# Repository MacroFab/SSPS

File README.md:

***
###SSPS
***
**MacroFab, INC. Super Simple Power Supply**

This repository contains the information and files needed to build the Super Simple Power Supply or SSPS. 

More information can be found on the [MacroFab, INC. blog](https://macrofab.com/blog/tag/ssps/). 

***
**License Information**

This project is under the [Creative Commons Attribution-ShareAlike 4.0 International License](LICENSE.md). These files are provided with no warranty and should be used at your own risk. 

***

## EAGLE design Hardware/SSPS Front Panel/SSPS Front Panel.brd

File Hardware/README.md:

***
###Hardware
***
**Hardware for the Super Simple Power Supply**

This repository contains the information and files needed to build the Super Simple Power Supply or SSPS. 

More information can be found on the [MacroFab, INC. blog](https://macrofab.com/blog/tag/ssps/). Specifications can be found [here](https://macrofab.com/blog/super-simple-power-supply-ssps-design-part-1/).

***
**License Information**

This project is under the [Creative Commons Attribution-ShareAlike 4.0 International License](LICENSE.md). These files are provided with no warranty and should be used at your own risk. 

***
**Directory listing of the repository**

| Directory | Description |
|---|---|
| Datasheets |  Datasheets that are a pain to get a hold of. |
| Enclosure | Enclosure Drawings and Mockups. | 
| OPA541 Breakout | Test board for the OPA541 Opamp. |
| SSPS Front Panel | Front Panel for the SSPS. Digital Controls. |
| SSPS Front Panel Test | Test board for the SSPS digital side. |
| SSPS Analog board | Analog output board |
| SSPS Regulated Power Supply Simulation | Multisim Simulation of the SSPS Analog side. |

***
**Credits**

Designed by:   
Parker Dillmann 
Stephen "Hackerman" Kraig 

Software by:   
Parker Dillmann  
Stephen "Hackerman" Kraig 

***

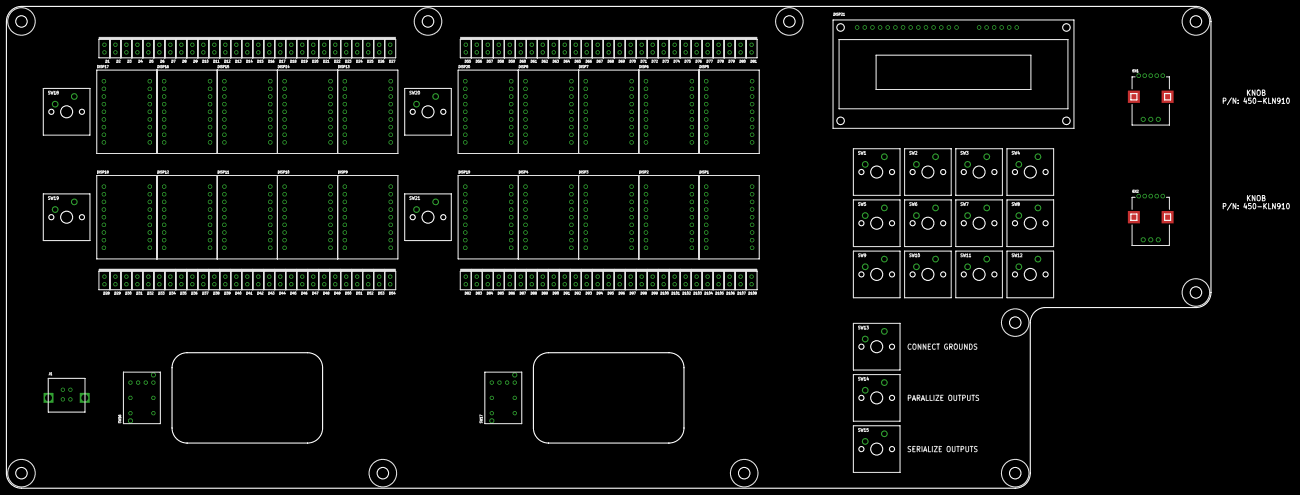
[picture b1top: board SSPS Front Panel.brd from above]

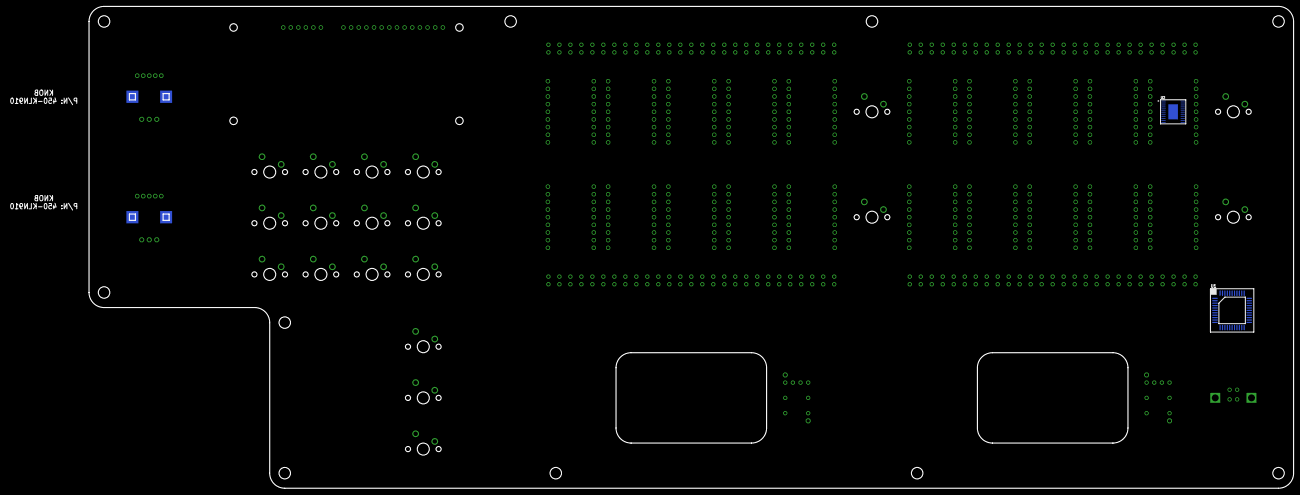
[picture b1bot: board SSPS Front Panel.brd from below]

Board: 2 copper layers, 400.0 x 160.0 mm, 165 parts (2 on the bottom side), 3 nets, no tracks yet.

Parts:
D1, D2, D3, D4, D5, D6, D7, D8, D9, D10, D11, D12, D13, D14, D15, D16, D17, D18, D19, D20, D21, D22, D23, D24, D25, D26, D27, D28, D29, D30, D31, D32, D33, D34, D35, D36, D37, D38, D39, D40, D41, D42, D43, D44, D45, D46, D47, D48, D49, D50, D51, D52, D53, D54, D55, D56, D57, D58, D59, D60, D61, D62, D63, D64, D65, D66, D67, D68, D69, D70, D71, D72, D73, D74, D75, D76, D77, D78, D79, D80, D81, D82, D83, D84, D85, D86, D87, D88, D89, D90, D91, D92, D93, D94, D95, D96, D97, D98, D99, D100, D101, D102, D103, D104, D105, D106, D107, D108: WP1043
DISP1, DISP2, DISP3, DISP4, DISP5, DISP6, DISP7, DISP8, DISP9, DISP10, DISP11, DISP12, DISP13, DISP14, DISP15, DISP16, DISP17, DISP18, DISP19, DISP20: PSA08-11GWA; PSA08-11SRWA
DISP21: CU16025-UWJ6; CU16025-UW6J
EN1, EN2: PEL12T-4226F-S1024; PEL12T
H1, H2, H3, H4, H5, H6, H7, H8, H9, H10: MOUNT_HOLE_150MIL
J1: 61400413321
SW1, SW2, SW3, SW4, SW5, SW6, SW7, SW8, SW9, SW10, SW11, SW12, SW13, SW14, SW15, SW18, SW19, SW20, SW21: MX1A
SW16, SW17: 5501
U1: P8X32A-Q44; LQFP44
U2: STP16CP05XTTR; STP16CP05XTTR_TTSOP-24

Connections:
SLD: J1.S1, J1.S2
VDD: U1.8, U1.18, U1.30, U1.40
VSS: U1.5, U1.17, U1.27, U1.39

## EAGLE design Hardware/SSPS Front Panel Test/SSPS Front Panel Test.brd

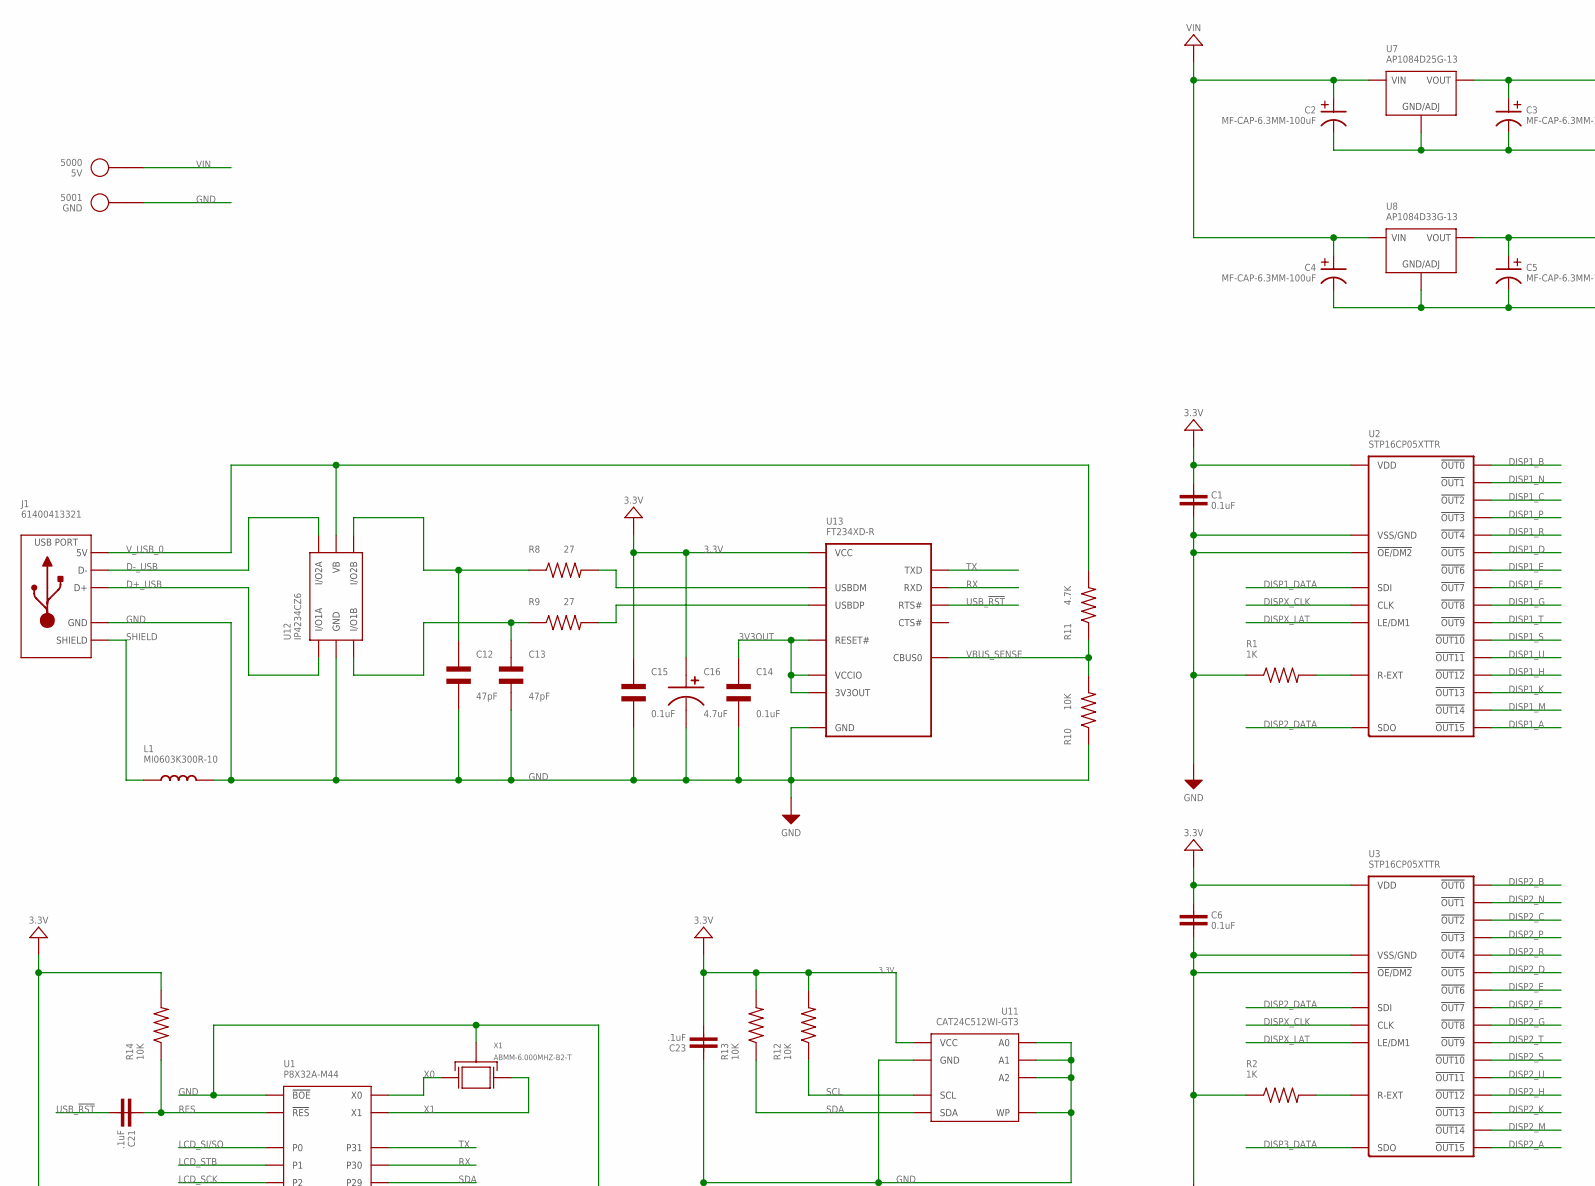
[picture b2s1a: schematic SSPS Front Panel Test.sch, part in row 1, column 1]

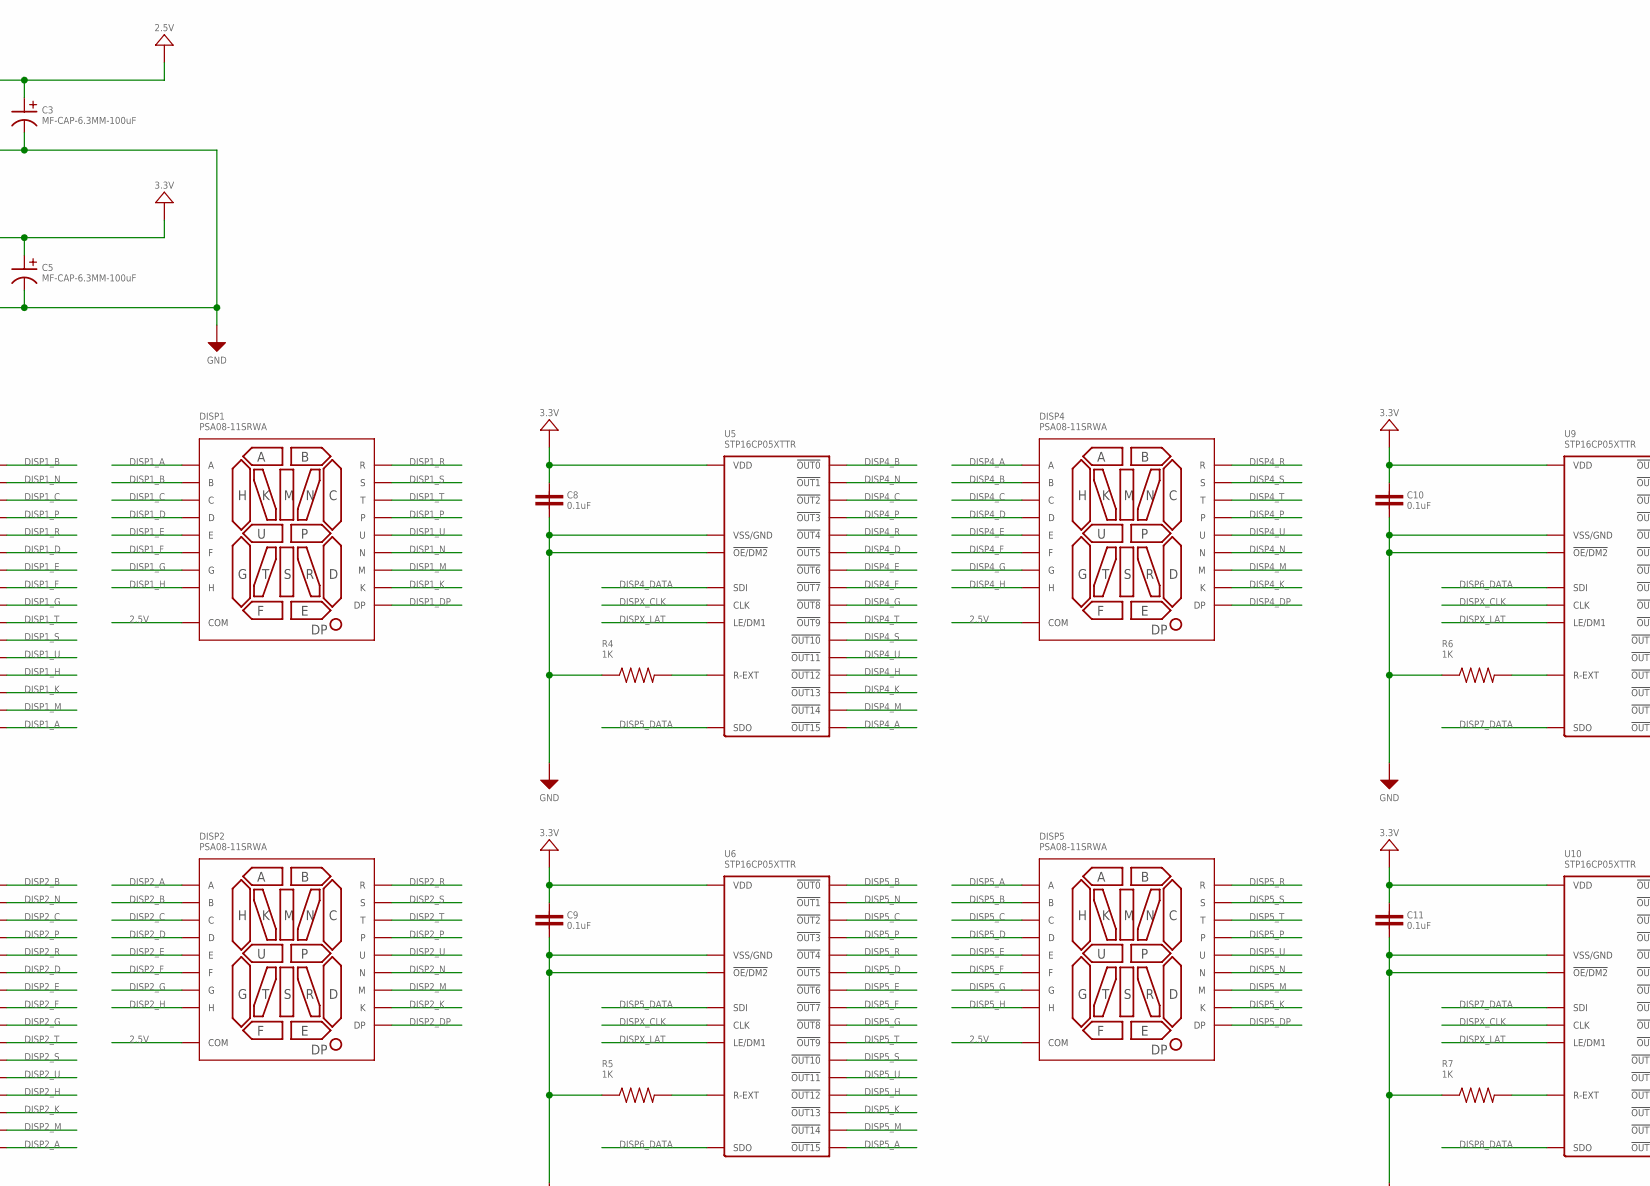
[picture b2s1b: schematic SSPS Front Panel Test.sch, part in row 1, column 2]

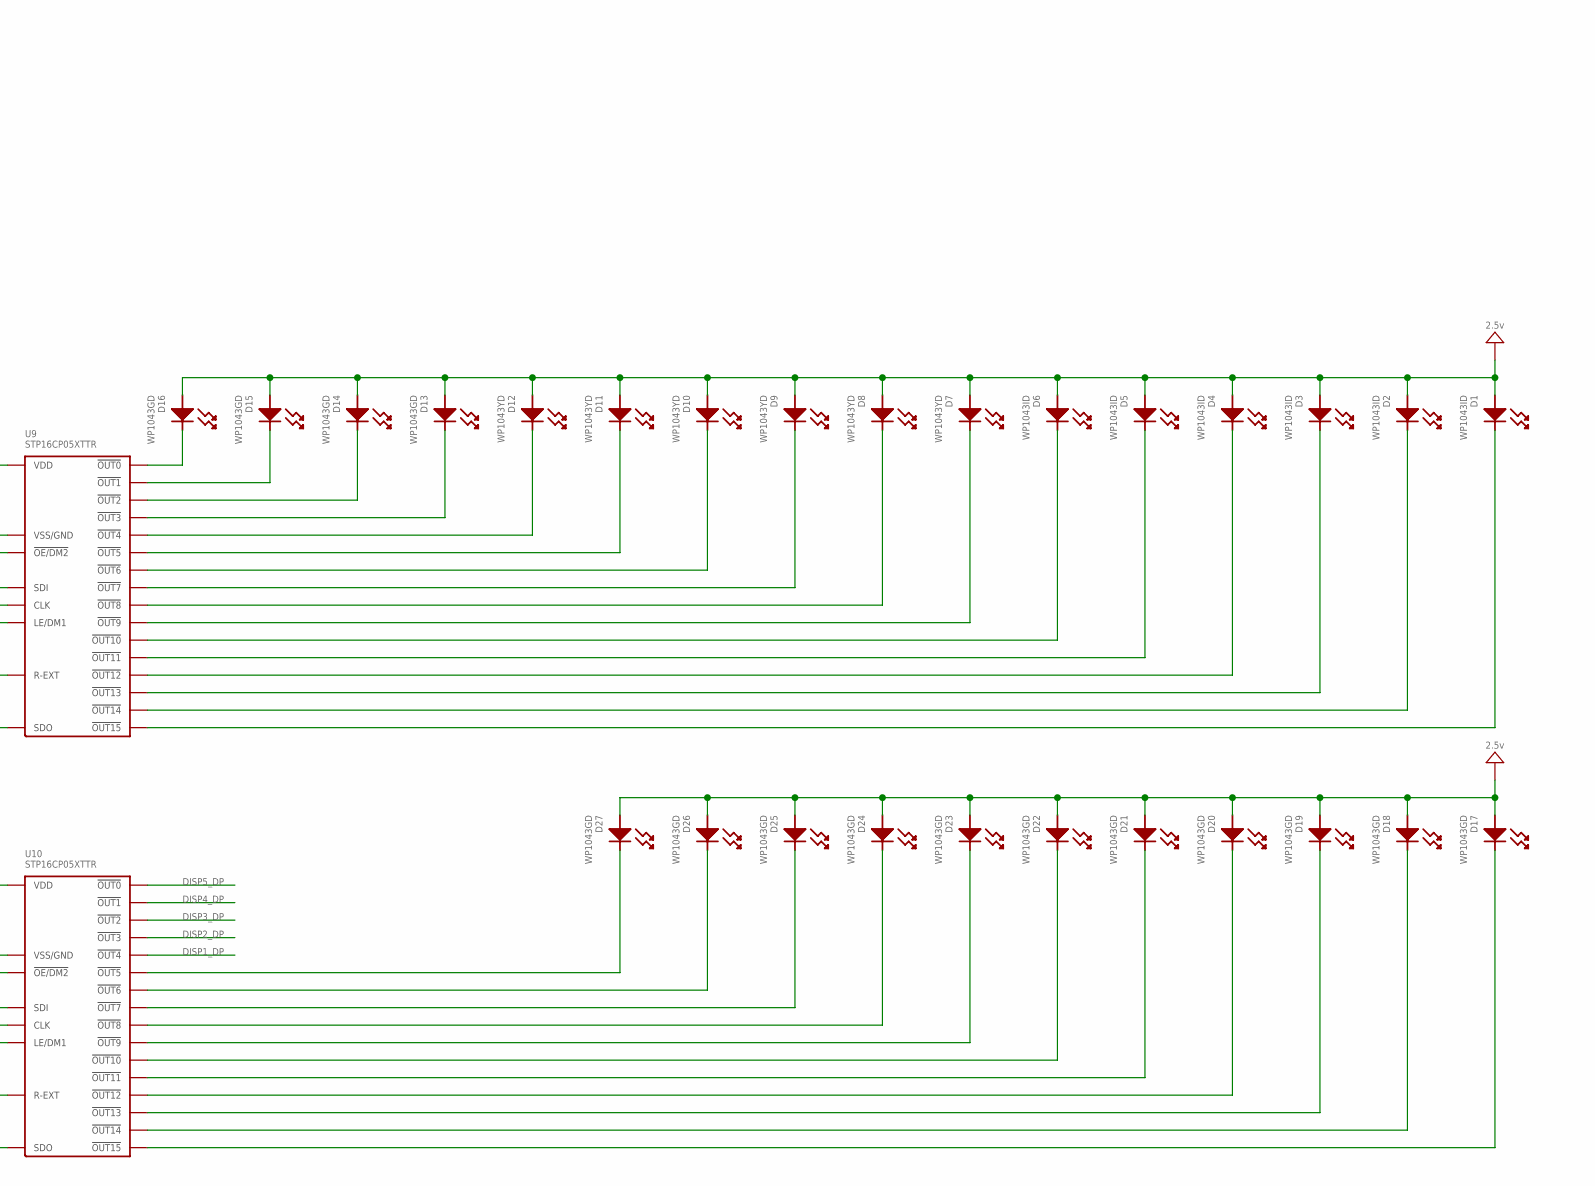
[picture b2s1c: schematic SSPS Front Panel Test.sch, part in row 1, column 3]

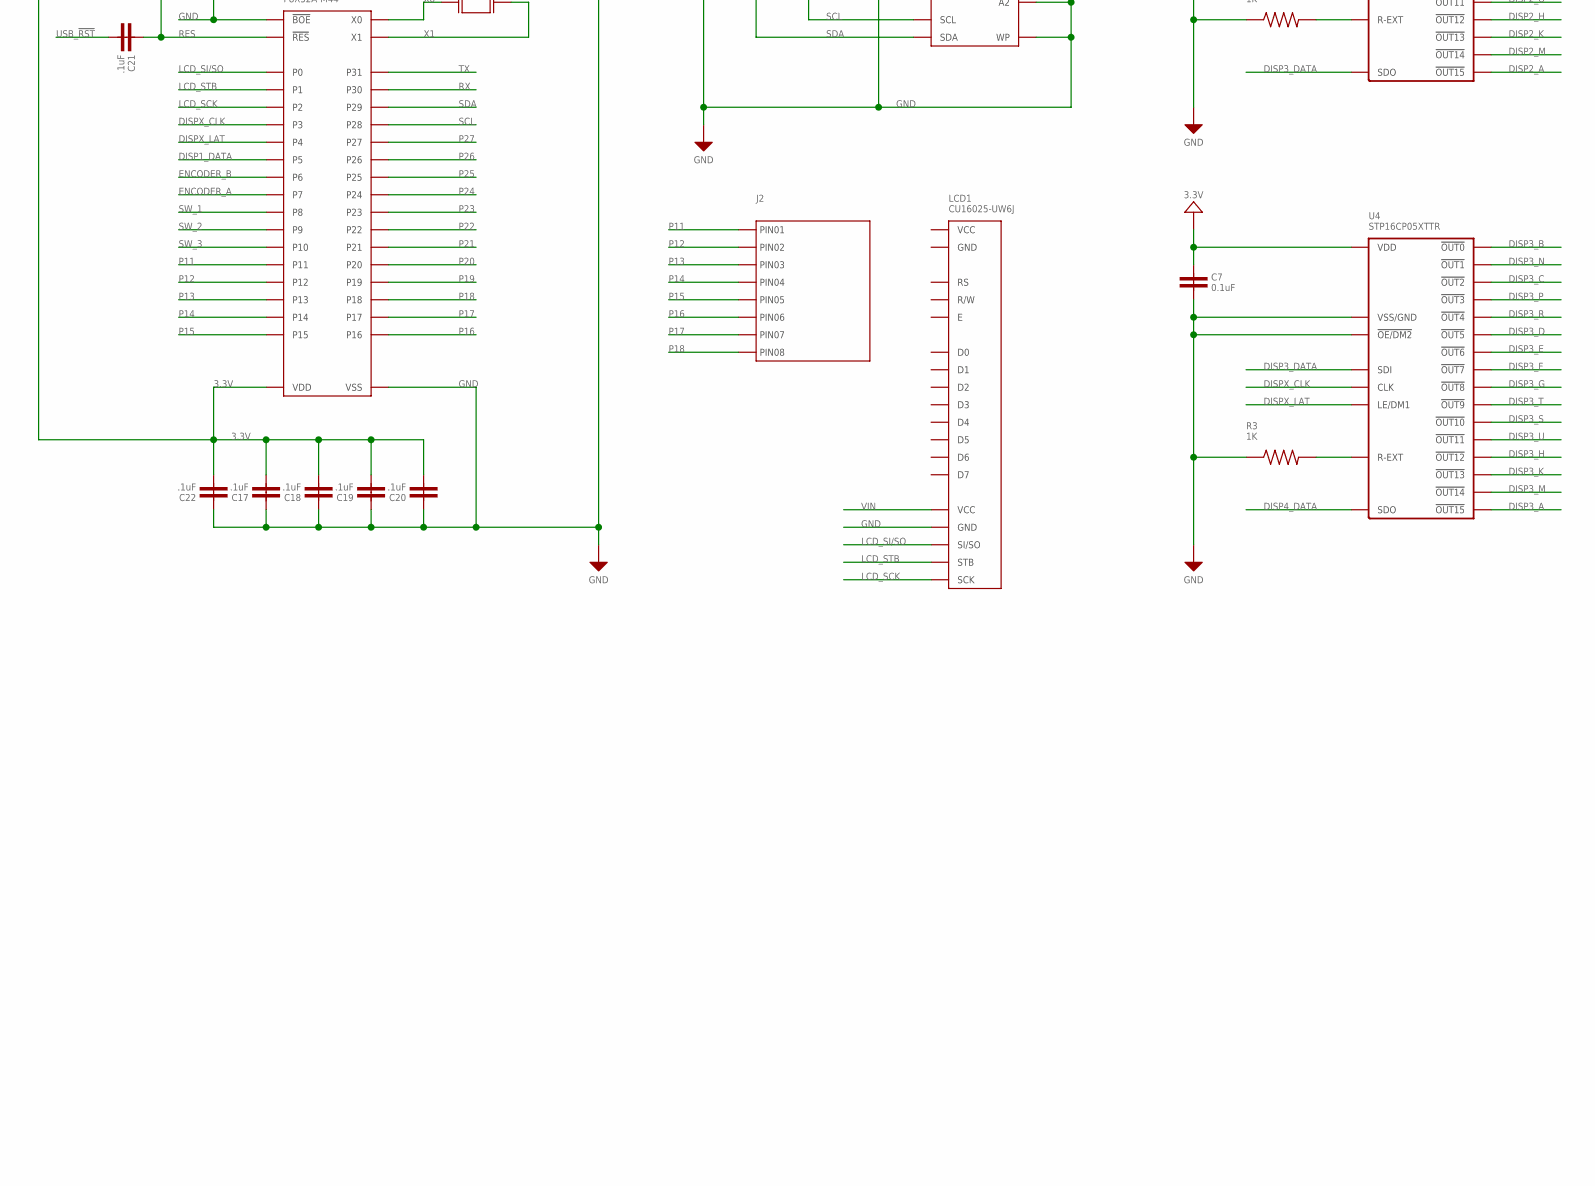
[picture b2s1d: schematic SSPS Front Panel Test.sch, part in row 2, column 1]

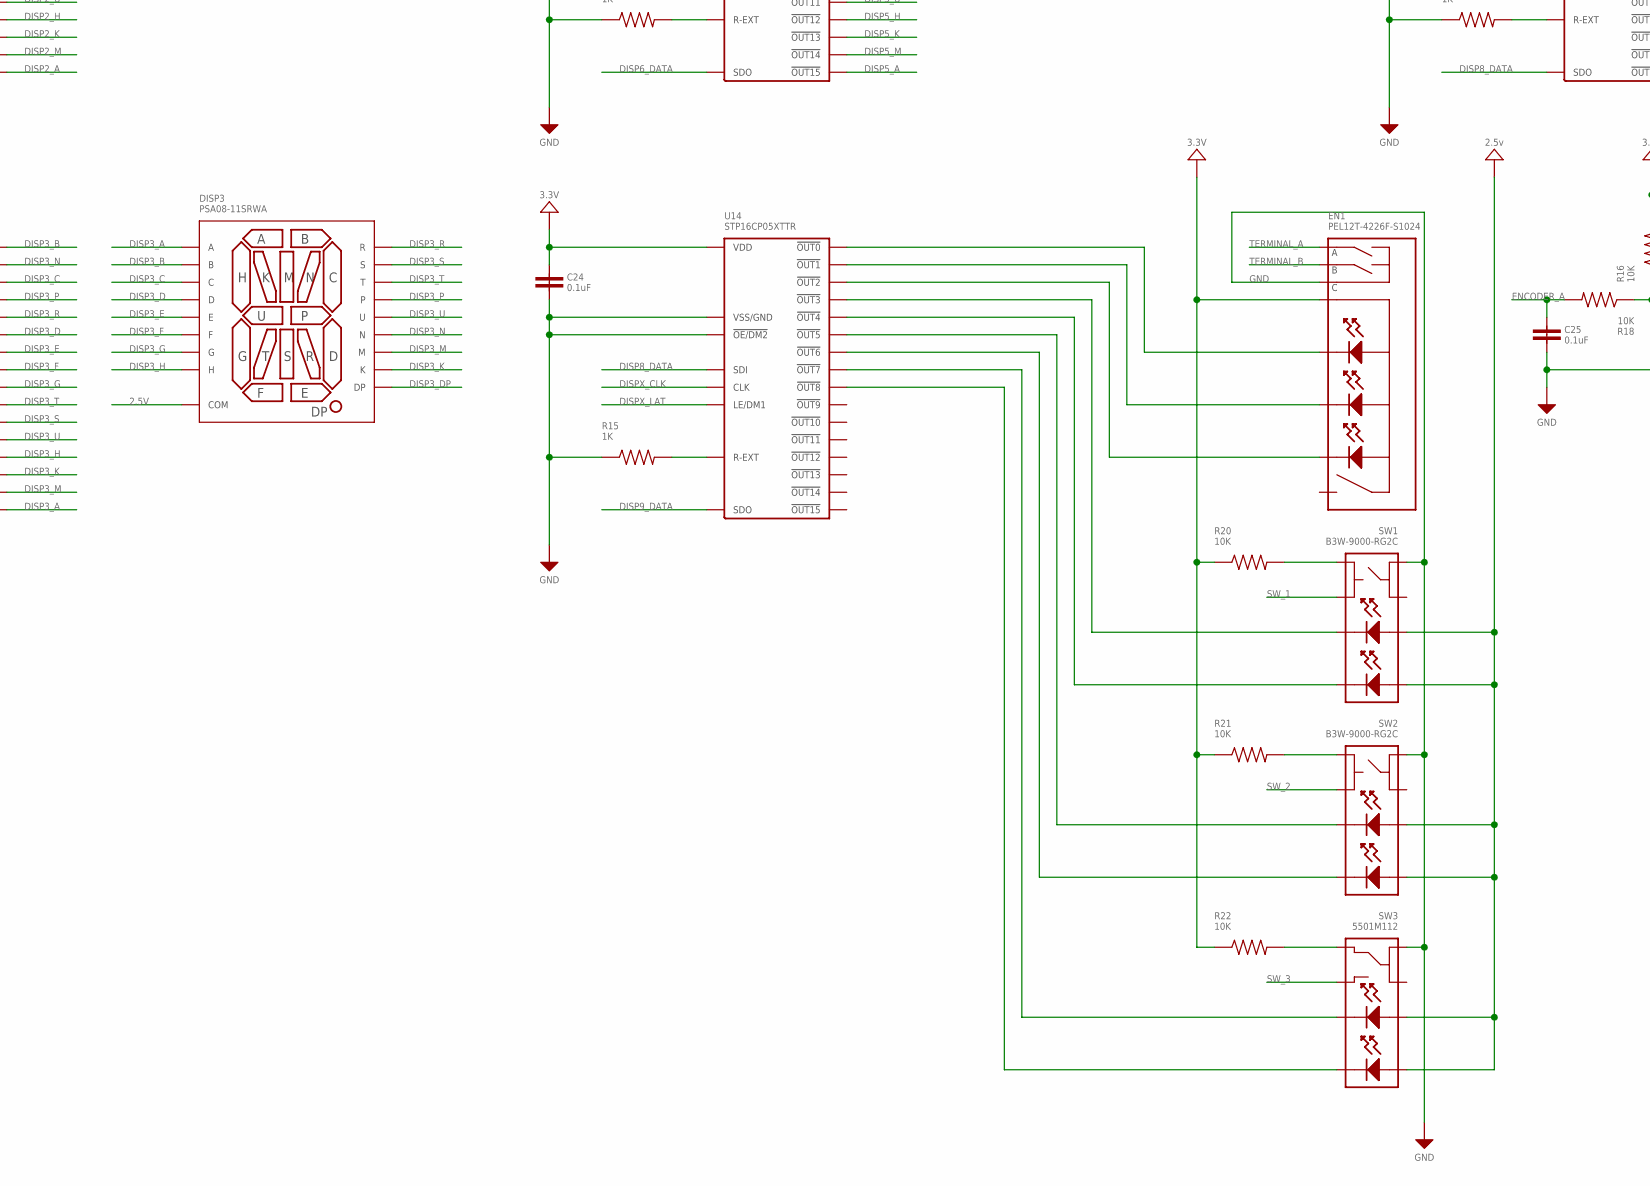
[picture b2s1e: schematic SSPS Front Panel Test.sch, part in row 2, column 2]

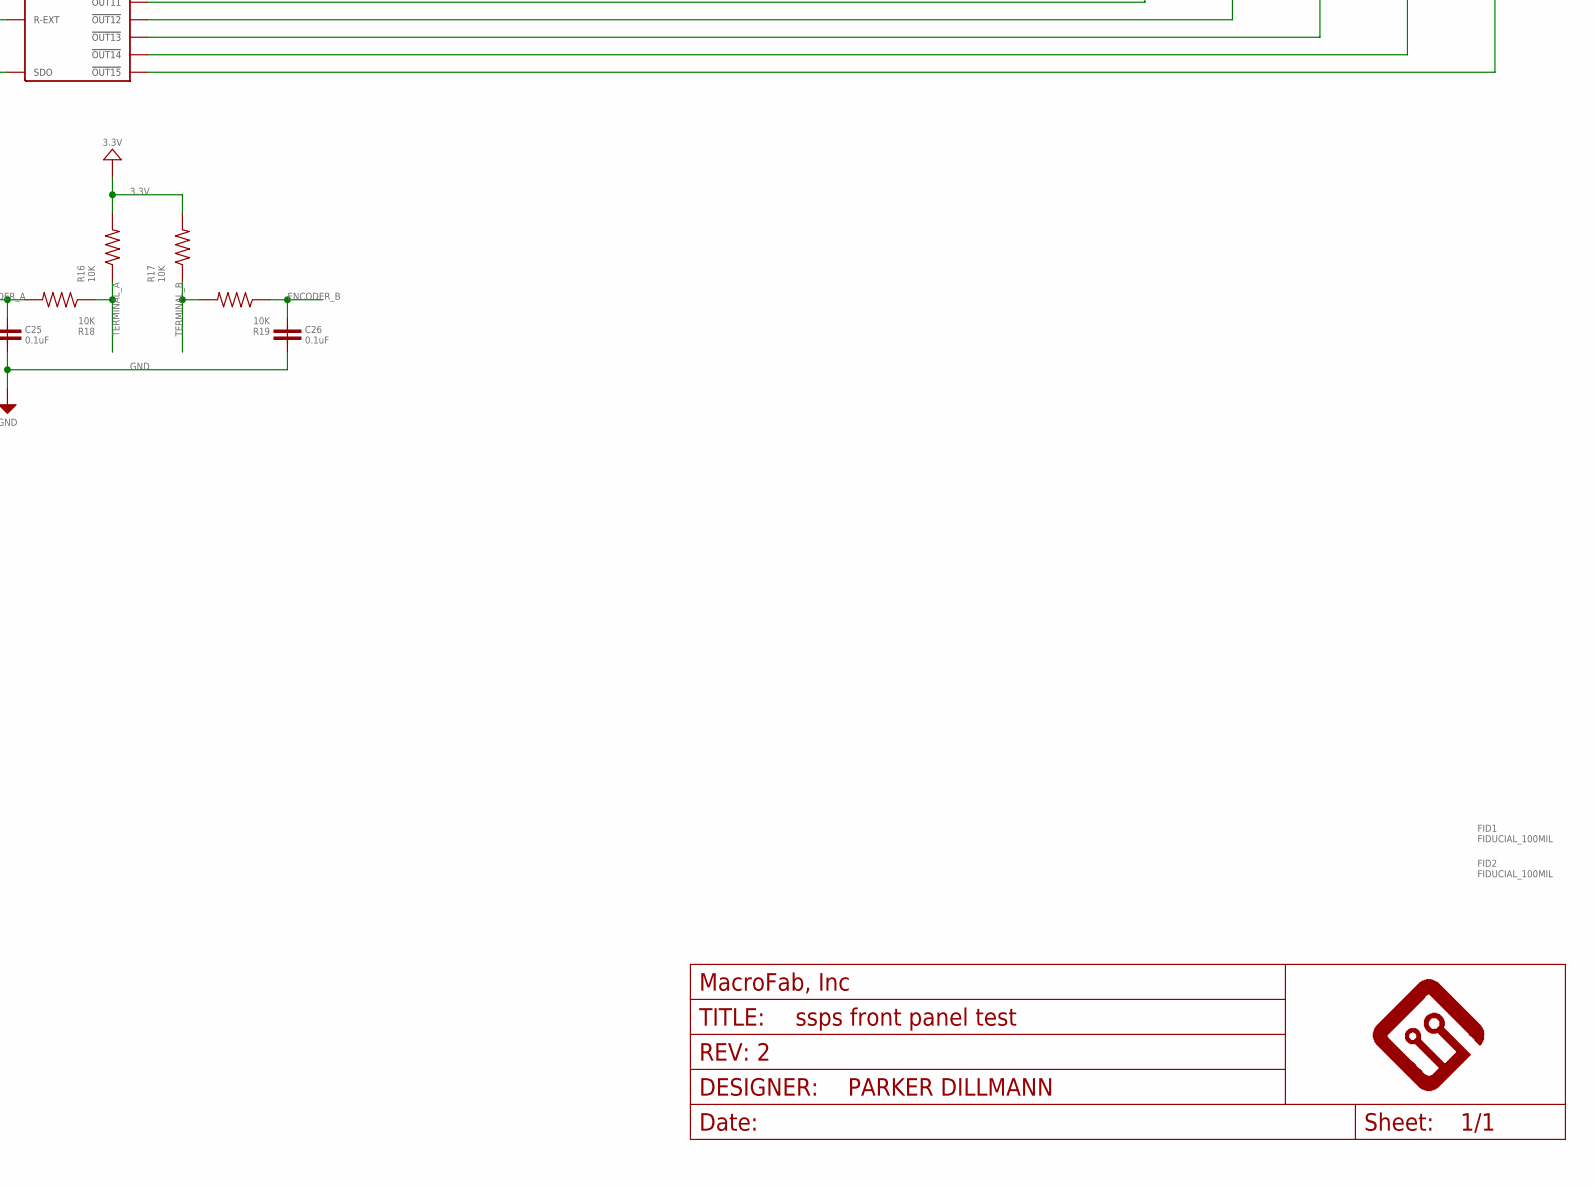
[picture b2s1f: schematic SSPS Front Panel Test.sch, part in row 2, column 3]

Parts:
5V: 5000; KEYSTONE_5115-5119
C1, C6, C7, C8, C9, C10, C11, C24, C25, C26: 0.1uF; 0603
C2, C3, C4, C5: MF-CAP-6.3MM-100uF; 6.3MM_CAP_SMD
C12, C13: 47pF; C0603
C14, C15: 0.1uF; C0603
C16: 4.7uF; CP4MM
C17, C18, C19, C20, C21, C22, C23: .1uF; 0603
D1, D2, D3, D4, D5, D6: WP1043ID; WP1043
D7, D8, D9, D10, D11, D12: WP1043YD; WP1043
D13, D14, D15, D16, D17, D18, D19, D20, D21, D22, D23, D24, D25, D26, D27: WP1043GD; WP1043
DISP1, DISP2, DISP3, DISP4, DISP5: PSA08-11SRWA
EN1: PEL12T-4226F-S1024; PEL12T
FID1, FID2: FIDUCIAL_100MIL
FRAME1: MF_FRAMEDEFAULT; MF_FRAME_DEFAULT
GND: 5001; KEYSTONE_5115-5119
J1: 61400413321
J2: CON_01X08_2.54MM_PIN_HEADER; 2.54MM_01X08_PIN_HEADER
L1: MI0603K300R-10; L0603
LCD1: CU16025-UW6J
R1, R2, R3, R4, R5, R6, R7, R15: 1K; 0603
R8, R9: 27; R0603
R10: 10K; R0603
R11: 4.7K; R0603
R12, R13, R14, R16, R17, R18, R19, R20, R21, R22: 10K; 0603
SW1, SW2: B3W-9000-RG2C; B3W-9000
SW3: 5501M112; 5501
U1: P8X32A-M44; P8X32A_QFN-44
U2, U3, U4, U5, U6, U9, U10, U14: STP16CP05XTTR; STP16CP05XTTR_TTSOP-24
U7: AP1084D25G-13; AP1084_TO-252-3L
U8: AP1084D33G-13; AP1084_TO-252-3L
U11: CAT24C512WI-GT3; SOIC-8_W
U12: IP4234CZ6; IP4234CZ6_SOT-457-6
U13: FT234XD-R; FT234X_DFN-12
X1: ABMM-6.000MHZ-B2-T; 7MMX5MM

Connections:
2.5V: C3.POS, D1.A (ANODE), D2.A (ANODE), D3.A (ANODE), D4.A (ANODE), D5.A (ANODE), D6.A (ANODE), D7.A (ANODE), D8.A (ANODE), D9.A (ANODE), D10.A (ANODE), D11.A (ANODE), D12.A (ANODE), D13.A (ANODE), D14.A (ANODE), D15.A (ANODE), D16.A (ANODE), D17.A (ANODE), D18.A (ANODE), D19.A (ANODE), D20.A (ANODE), D21.A (ANODE), D22.A (ANODE), D23.A (ANODE), D24.A (ANODE), D25.A (ANODE), D26.A (ANODE), D27.A (ANODE), DISP1.P$11 (COM), DISP2.P$11 (COM), DISP3.P$11 (COM), DISP4.P$11 (COM), DISP5.P$11 (COM), SW1.ANODE_1, SW1.ANODE_2, SW2.ANODE_1, SW2.ANODE_2, SW3.ANODE_1, SW3.ANODE_2, U7.3 (OUT)
3.3V: C1.1, C5.POS, C6.1, C7.1, C8.1, C9.1, C10.1, C11.1, C15.P$1, C16.P$1, C17.2, C18.2, C19.2, C20.2, C22.2, C23.2, C24.1, EN1.5, R12.2, R13.2, R14.2, R16.2, R17.2, R20.1, R21.1, R22.1, U1.8 (VDD), U1.18 (VDD), U1.30 (VDD), U1.40 (VDD), U2.P$24 (VDD), U3.P$24 (VDD), U4.P$24 (VDD), U5.P$24 (VDD), U6.P$24 (VDD), U8.3 (OUT), U9.P$24 (VDD), U10.P$24 (VDD), U11.8 (VCC), U13.4 (VCC), U14.P$24 (VDD)
3V3OUT: C14.P$1, U13.2 (RESET#), U13.3 (3V3OUT), U13.9 (VCCIO)
D+_USB: J1.3 (D+), U12.1 (I/O1A)
D-_USB: J1.2 (D-), U12.6 (I/O2A)
DISP1_A: DISP1.P$1 (A), U2.P$20 (!OUT15)
DISP1_B: DISP1.P$18 (B), U2.P$5 (!OUT0)
DISP1_C: DISP1.P$16 (C), U2.P$7 (!OUT2)
DISP1_D: DISP1.P$13 (D), U2.P$10 (!OUT5)
DISP1_DATA: U1.2 (P5), U2.P$2 (SDI)
DISP1_DP: DISP1.P$12 (DP), U10.P$9 (!OUT4)
DISP1_E: DISP1.P$10 (E), U2.P$11 (!OUT6)
DISP1_F: DISP1.P$9 (F), U2.P$12 (!OUT7)
DISP1_G: DISP1.P$8 (G), U2.P$13 (!OUT8)
DISP1_H: DISP1.P$4 (H), U2.P$17 (!OUT12)
DISP1_K: DISP1.P$3 (K), U2.P$18 (!OUT13)
DISP1_M: DISP1.P$2 (M), U2.P$19 (!OUT14)
DISP1_N: DISP1.P$17 (N), U2.P$6 (!OUT1)
DISP1_P: DISP1.P$15, U2.P$8 (!OUT3)
DISP1_R: DISP1.P$14 (R), U2.P$9 (!OUT4)
DISP1_S: DISP1.P$6 (S), U2.P$15 (!OUT10)
DISP1_T: DISP1.P$7 (T), U2.P$14 (!OUT9)
DISP1_U: DISP1.P$5 (U), U2.P$16 (!OUT11)
DISP2_A: DISP2.P$1 (A), U3.P$20 (!OUT15)
DISP2_B: DISP2.P$18 (B), U3.P$5 (!OUT0)
DISP2_C: DISP2.P$16 (C), U3.P$7 (!OUT2)
DISP2_D: DISP2.P$13 (D), U3.P$10 (!OUT5)
DISP2_DATA: U2.P$22 (SDO), U3.P$2 (SDI)
DISP2_DP: DISP2.P$12 (DP), U10.P$8 (!OUT3)
DISP2_E: DISP2.P$10 (E), U3.P$11 (!OUT6)
DISP2_F: DISP2.P$9 (F), U3.P$12 (!OUT7)
DISP2_G: DISP2.P$8 (G), U3.P$13 (!OUT8)
DISP2_H: DISP2.P$4 (H), U3.P$17 (!OUT12)
DISP2_K: DISP2.P$3 (K), U3.P$18 (!OUT13)
DISP2_M: DISP2.P$2 (M), U3.P$19 (!OUT14)
DISP2_N: DISP2.P$17 (N), U3.P$6 (!OUT1)
DISP2_P: DISP2.P$15, U3.P$8 (!OUT3)
DISP2_R: DISP2.P$14 (R), U3.P$9 (!OUT4)
DISP2_S: DISP2.P$6 (S), U3.P$15 (!OUT10)
DISP2_T: DISP2.P$7 (T), U3.P$14 (!OUT9)
DISP2_U: DISP2.P$5 (U), U3.P$16 (!OUT11)
DISP3_A: DISP3.P$1 (A), U4.P$20 (!OUT15)
DISP3_B: DISP3.P$18 (B), U4.P$5 (!OUT0)
DISP3_C: DISP3.P$16 (C), U4.P$7 (!OUT2)
DISP3_D: DISP3.P$13 (D), U4.P$10 (!OUT5)
DISP3_DATA: U3.P$22 (SDO), U4.P$2 (SDI)
DISP3_DP: DISP3.P$12 (DP), U10.P$7 (!OUT2)
DISP3_E: DISP3.P$10 (E), U4.P$11 (!OUT6)
DISP3_F: DISP3.P$9 (F), U4.P$12 (!OUT7)
DISP3_G: DISP3.P$8 (G), U4.P$13 (!OUT8)
DISP3_H: DISP3.P$4 (H), U4.P$17 (!OUT12)
DISP3_K: DISP3.P$3 (K), U4.P$18 (!OUT13)
DISP3_M: DISP3.P$2 (M), U4.P$19 (!OUT14)
DISP3_N: DISP3.P$17 (N), U4.P$6 (!OUT1)
DISP3_P: DISP3.P$15, U4.P$8 (!OUT3)
DISP3_R: DISP3.P$14 (R), U4.P$9 (!OUT4)
DISP3_S: DISP3.P$6 (S), U4.P$15 (!OUT10)
DISP3_T: DISP3.P$7 (T), U4.P$14 (!OUT9)
DISP3_U: DISP3.P$5 (U), U4.P$16 (!OUT11)
DISP4_A: DISP4.P$1 (A), U5.P$20 (!OUT15)
DISP4_B: DISP4.P$18 (B), U5.P$5 (!OUT0)
DISP4_C: DISP4.P$16 (C), U5.P$7 (!OUT2)
DISP4_D: DISP4.P$13 (D), U5.P$10 (!OUT5)
DISP4_DATA: U4.P$22 (SDO), U5.P$2 (SDI)
DISP4_DP: DISP4.P$12 (DP), U10.P$6 (!OUT1)
DISP4_E: DISP4.P$10 (E), U5.P$11 (!OUT6)
DISP4_F: DISP4.P$9 (F), U5.P$12 (!OUT7)
DISP4_G: DISP4.P$8 (G), U5.P$13 (!OUT8)
DISP4_H: DISP4.P$4 (H), U5.P$17 (!OUT12)
DISP4_K: DISP4.P$3 (K), U5.P$18 (!OUT13)
DISP4_M: DISP4.P$2 (M), U5.P$19 (!OUT14)
DISP4_N: DISP4.P$17 (N), U5.P$6 (!OUT1)
DISP4_P: DISP4.P$15, U5.P$8 (!OUT3)
DISP4_R: DISP4.P$14 (R), U5.P$9 (!OUT4)
DISP4_S: DISP4.P$6 (S), U5.P$15 (!OUT10)
DISP4_T: DISP4.P$7 (T), U5.P$14 (!OUT9)
DISP4_U: DISP4.P$5 (U), U5.P$16 (!OUT11)
DISP5_A: DISP5.P$1 (A), U6.P$20 (!OUT15)
DISP5_B: DISP5.P$18 (B), U6.P$5 (!OUT0)
DISP5_C: DISP5.P$16 (C), U6.P$7 (!OUT2)
DISP5_D: DISP5.P$13 (D), U6.P$10 (!OUT5)
DISP5_DATA: U5.P$22 (SDO), U6.P$2 (SDI)
DISP5_DP: DISP5.P$12 (DP), U10.P$5 (!OUT0)
DISP5_E: DISP5.P$10 (E), U6.P$11 (!OUT6)
DISP5_F: DISP5.P$9 (F), U6.P$12 (!OUT7)
DISP5_G: DISP5.P$8 (G), U6.P$13 (!OUT8)
DISP5_H: DISP5.P$4 (H), U6.P$17 (!OUT12)
DISP5_K: DISP5.P$3 (K), U6.P$18 (!OUT13)
DISP5_M: DISP5.P$2 (M), U6.P$19 (!OUT14)
DISP5_N: DISP5.P$17 (N), U6.P$6 (!OUT1)
DISP5_P: DISP5.P$15, U6.P$8 (!OUT3)
DISP5_R: DISP5.P$14 (R), U6.P$9 (!OUT4)
DISP5_S: DISP5.P$6 (S), U6.P$15 (!OUT10)
DISP5_T: DISP5.P$7 (T), U6.P$14 (!OUT9)
DISP5_U: DISP5.P$5 (U), U6.P$16 (!OUT11)
DISP6_DATA: U6.P$22 (SDO), U9.P$2 (SDI)
DISP7_DATA: U9.P$22 (SDO), U10.P$2 (SDI)
DISP8_DATA: U10.P$22 (SDO), U14.P$2 (SDI)
DISP9_DATA: U14.P$22 (SDO)
DISPX_CLK: U1.44 (P3), U2.P$3 (CLK), U3.P$3 (CLK), U4.P$3 (CLK), U5.P$3 (CLK), U6.P$3 (CLK), U9.P$3 (CLK), U10.P$3 (CLK), U14.P$3 (CLK)
DISPX_LAT: U1.1 (P4), U2.P$4 (LE/DM1), U3.P$4 (LE/DM1), U4.P$4 (LE/DM1), U5.P$4 (LE/DM1), U6.P$4 (LE/DM1), U9.P$4 (LE/DM1), U10.P$4 (LE/DM1), U14.P$4 (LE/DM1)
ENCODER_A: C25.1, R18.2, U1.4 (P7)
ENCODER_B: C26.1, R19.1, U1.3 (P6)
GND: C1.2, C2.NEG, C3.NEG, C4.NEG, C5.NEG, C6.2, C7.2, C8.2, C9.2, C10.2, C11.2, C12.P$2, C13.P$2, C14.P$2, C15.P$2, C16.P$2, C17.1, C18.1, C19.1, C20.1, C22.1, C23.1, C24.2, C25.2, C26.2, EN1.C, GND.P$1, J1.4 (GND), L1.P$2, LCD1.P$18 (GND2), R1.1, R2.1, R3.1, R4.1, R5.1, R6.1, R7.1, R10.P$1, R15.1, SW1.1, SW2.1, SW3.1A, U1.5 (VSS), U1.6 (!BOE), U1.17 (VSS), U1.27 (VSS), U1.39 (VSS), U2.P$1 (VSS/GND), U2.P$21 (!OE/DM2), U2.PAD (VSS/GND), U3.P$1 (VSS/GND), U3.P$21 (!OE/DM2), U3.PAD (VSS/GND), U4.P$1 (VSS/GND), U4.P$21 (!OE/DM2), U4.PAD (VSS/GND), U5.P$1 (VSS/GND), U5.P$21 (!OE/DM2), U5.PAD (VSS/GND), U6.P$1 (VSS/GND), U6.P$21 (!OE/DM2), U6.PAD (VSS/GND), U7.1 (GND), U8.1 (GND), U9.P$1 (VSS/GND), U9.P$21 (!OE/DM2), U9.PAD (VSS/GND), U10.P$1 (VSS/GND), U10.P$21 (!OE/DM2), U10.PAD (VSS/GND), U11.1 (A0), U11.2 (A1), U11.3 (A2), U11.4 (GND), U11.7 (WP), U12.2 (GND), U13.5 (GND), U13.P$1 (GND), U14.P$1 (VSS/GND), U14.P$21 (!OE/DM2), U14.PAD (VSS/GND), X1.P$2 (GND), X1.P$4 (GND)
LCD_SCK: LCD1.P$16 (SCK), U1.43 (P2)
LCD_SI/SO: LCD1.P$19 (SI/SO), U1.41 (P0)
LCD_STB: LCD1.P$17 (STB), U1.42 (P1)
unnamed: R1.2, U2.P$23 (R-EXT)
unnamed: R2.2, U3.P$23 (R-EXT)
unnamed: R3.2, U4.P$23 (R-EXT)
unnamed: R4.2, U5.P$23 (R-EXT)
unnamed: R5.2, U6.P$23 (R-EXT)
unnamed: R6.2, U9.P$23 (R-EXT)
unnamed: D16.C (CATHODE), U9.P$5 (!OUT0)
unnamed: D15.C (CATHODE), U9.P$6 (!OUT1)
unnamed: D14.C (CATHODE), U9.P$7 (!OUT2)
unnamed: D13.C (CATHODE), U9.P$8 (!OUT3)
unnamed: D12.C (CATHODE), U9.P$9 (!OUT4)
unnamed: D17.C (CATHODE), U10.P$20 (!OUT15)
unnamed: D10.C (CATHODE), U9.P$11 (!OUT6)
unnamed: D9.C (CATHODE), U9.P$12 (!OUT7)
unnamed: D8.C (CATHODE), U9.P$13 (!OUT8)
unnamed: D7.C (CATHODE), U9.P$14 (!OUT9)
unnamed: D6.C (CATHODE), U9.P$15 (!OUT10)
unnamed: D5.C (CATHODE), U9.P$16 (!OUT11)
unnamed: D4.C (CATHODE), U9.P$17 (!OUT12)
unnamed: D3.C (CATHODE), U9.P$18 (!OUT13)
unnamed: D2.C (CATHODE), U9.P$19 (!OUT14)
unnamed: D1.C (CATHODE), U9.P$20 (!OUT15)
unnamed: R7.2, U10.P$23 (R-EXT)
unnamed: D18.C (CATHODE), U10.P$19 (!OUT14)
unnamed: D19.C (CATHODE), U10.P$18 (!OUT13)
unnamed: D20.C (CATHODE), U10.P$17 (!OUT12)
unnamed: D21.C (CATHODE), U10.P$16 (!OUT11)
unnamed: D22.C (CATHODE), U10.P$15 (!OUT10)
unnamed: D23.C (CATHODE), U10.P$14 (!OUT9)
unnamed: D24.C (CATHODE), U10.P$13 (!OUT8)
unnamed: D25.C (CATHODE), U10.P$12 (!OUT7)
unnamed: D26.C (CATHODE), U10.P$11 (!OUT6)
unnamed: D27.C (CATHODE), U10.P$10 (!OUT5)
unnamed: R8.P$2, U13.1 (USBDM)
unnamed: D11.C (CATHODE), U9.P$10 (!OUT5)
unnamed: R9.P$2, U13.12 (USBDP)
unnamed: C12.P$1, R8.P$1, U12.4 (I/O2B)
unnamed: C13.P$1, R9.P$1, U12.3 (I/O1B)
unnamed: R15.2, U14.P$23 (R-EXT)
unnamed: EN1.1, U14.P$5 (!OUT0)
unnamed: EN1.2, U14.P$6 (!OUT1)
unnamed: EN1.4, U14.P$7 (!OUT2)
unnamed: SW1.CATHODE_1, U14.P$8 (!OUT3)
unnamed: SW1.CATHODE_2, U14.P$9 (!OUT4)
unnamed: SW2.CATHODE_1, U14.P$10 (!OUT5)
unnamed: SW2.CATHODE_2, U14.P$11 (!OUT6)
unnamed: SW3.CATHODE_1, U14.P$12 (!OUT7)
unnamed: SW3.CATHODE_2, U14.P$13 (!OUT8)
unnamed: R20.2, SW1.3
unnamed: R21.2, SW2.3
unnamed: R22.2, SW3.2
P11: J2.1, U1.12 (P11)
P12: J2.2, U1.13 (P12)
P13: J2.3, U1.14 (P13)
P14: J2.4, U1.15 (P14)
P15: J2.5, U1.16 (P15)
P16: J2.6, U1.19 (P16)
P17: J2.7, U1.20 (P17)
P18: J2.8, U1.21 (P18)
P19: U1.22 (P19)
P20: U1.23 (P20)
P21: U1.24 (P21)
P22: U1.25 (P22)
P23: U1.26 (P23)
P24: U1.31 (P24)
P25: U1.32 (P25)
P26: U1.33 (P26)
P27: U1.34 (P27)
RES: C21.1, R14.1, U1.7 (!RES)
RX: U1.37 (P30), U13.10 (RXD)
SCL: R12.1, U1.35 (P28), U11.6 (SCL)
SDA: R13.1, U1.36 (P29), U11.5 (SDA)
SHIELD: J1.S1 (SLD), J1.S2 (SLD), L1.P$1
SW_1: SW1.4, U1.9 (P8)
SW_2: SW2.4, U1.10 (P9)
SW_3: SW3.3, U1.11 (P10)
TERMINAL_A: EN1.A, R16.1, R18.1
TERMINAL_B: EN1.B, R17.1, R19.2
TX: U1.38 (P31), U13.7 (TXD)
USB_!RST: C21.2, U13.8 (RTS#)
VBUS_SENSE: R10.P$2, R11.P$1, U13.6 (CBUS0)
VIN: 5V.P$1, C2.POS, C4.POS, LCD1.P$20 (VCC2), U7.2 (IN), U8.2 (IN)
V_USB_0: J1.1 (5V), R11.P$2, U12.5 (VB)
X0: U1.29 (X0), X1.P$3 (X1)
X1: U1.28 (X1), X1.P$1 (X0)

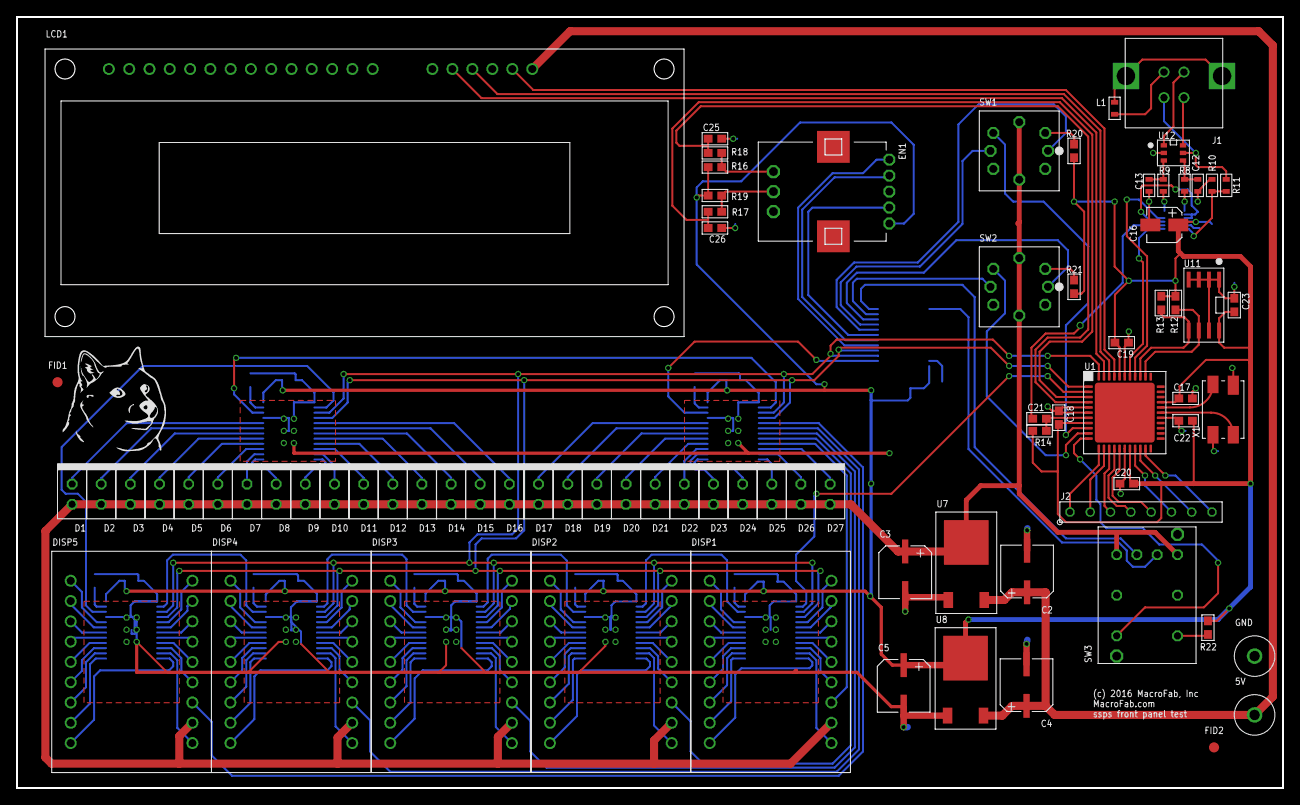
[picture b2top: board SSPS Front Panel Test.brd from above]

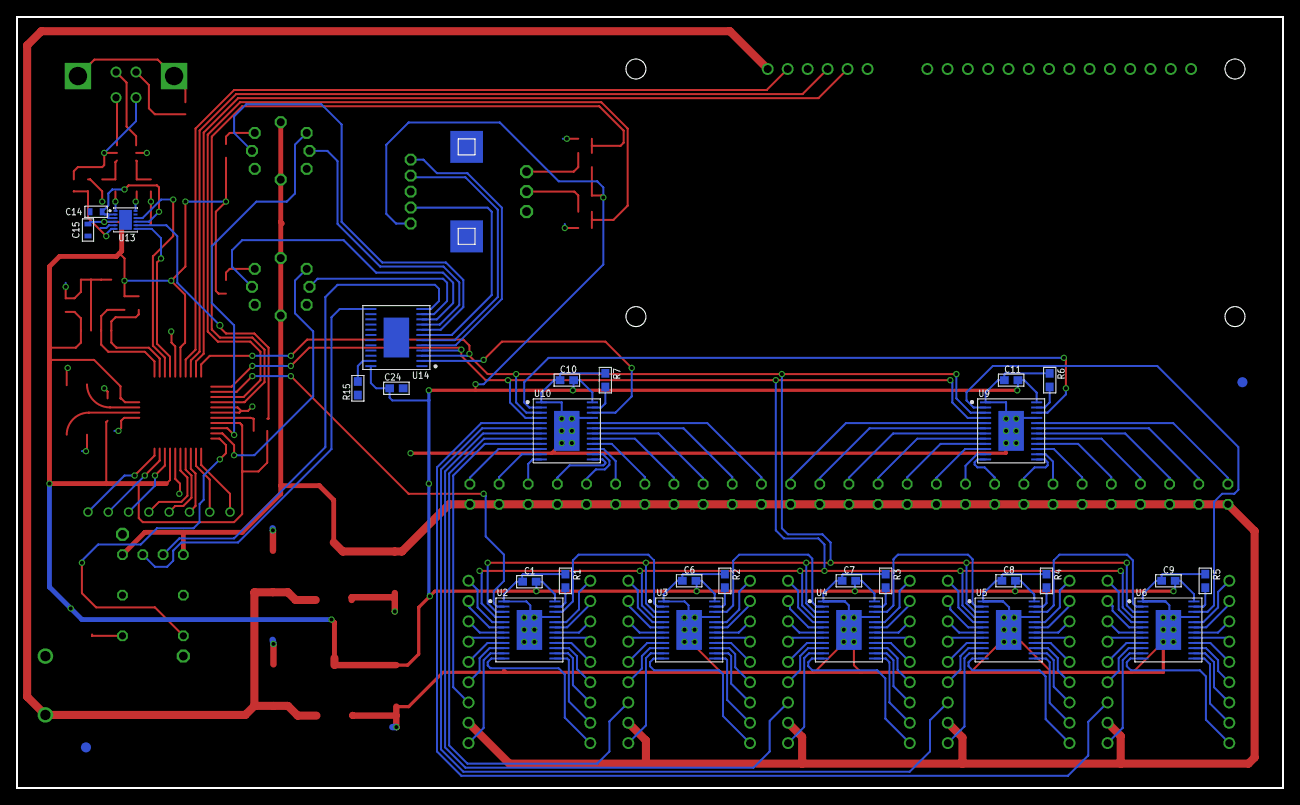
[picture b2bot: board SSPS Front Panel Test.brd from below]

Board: 2 copper layers, 158.5 x 96.5 mm, 108 parts (27 on the bottom side), 182 nets.

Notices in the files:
parts and their libraries:
MF_Aesthetics: (c) 2016 MacroFab, Inc
